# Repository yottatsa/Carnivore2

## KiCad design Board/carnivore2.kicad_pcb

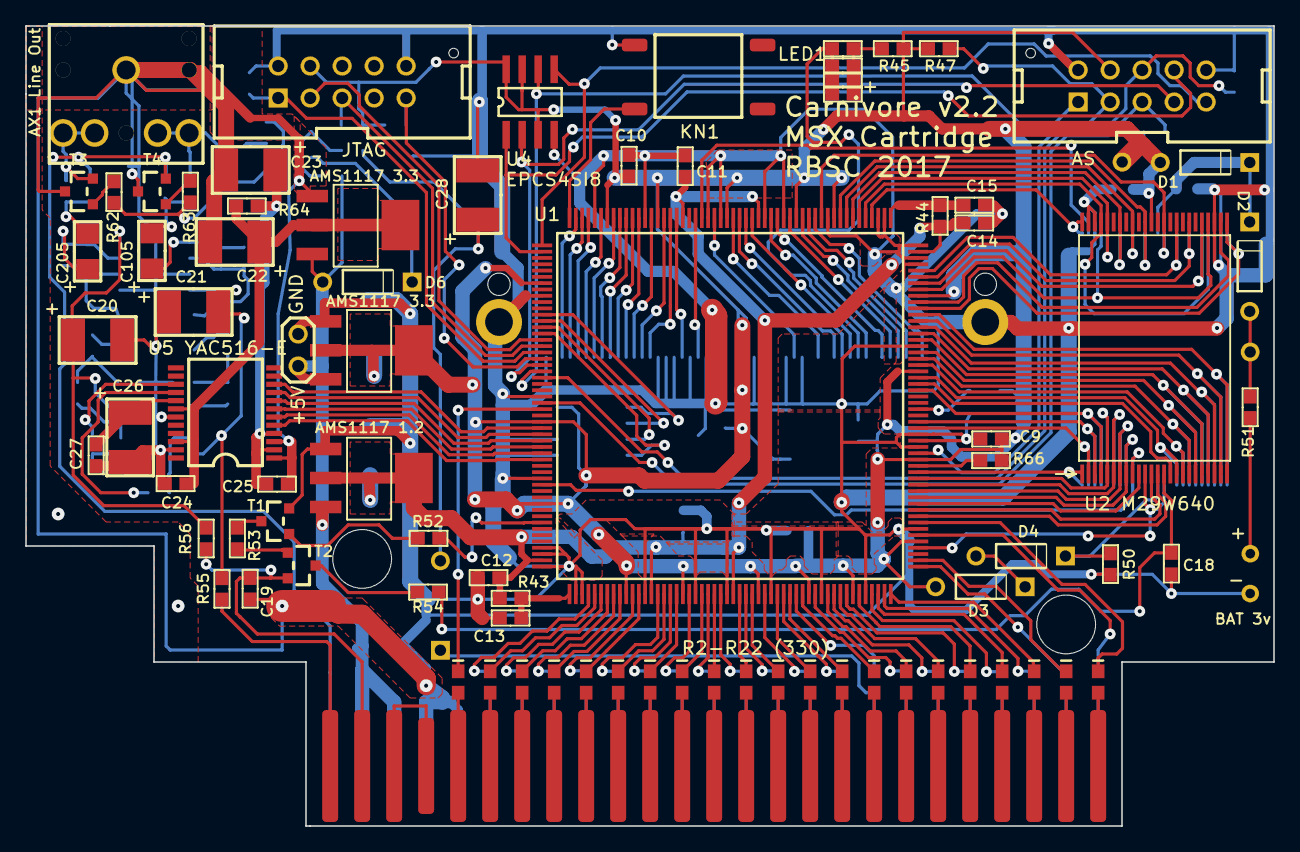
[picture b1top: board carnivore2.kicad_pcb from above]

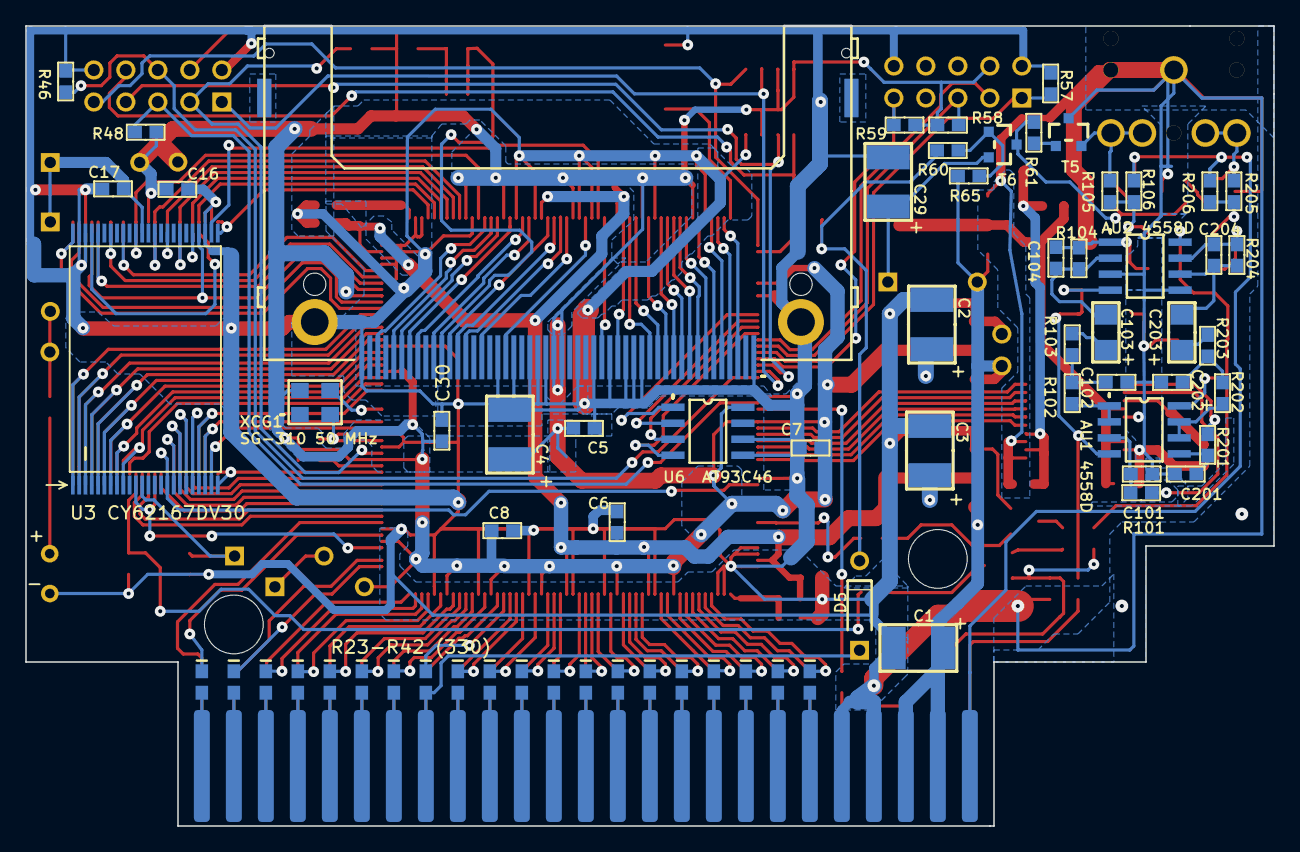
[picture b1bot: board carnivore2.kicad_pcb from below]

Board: 2 copper layers, 99.1 x 63.5 mm, 151 parts (69 on the bottom side), 220 nets.

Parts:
.1: KNS01_1
.2: EDGE50/MSX_1
.3: JUMPER_1
.6, .7: IDC10M_1
AU1, AU2: 4558D_1
AX1: {Value}; ST-222_1
C1, C2, C3, C4, C22, C23, C26, C28: 10mk; C_1812_1
C5, C6, C7, C8, C9, C10, C11, C12, C13, C14, C15, C16, C17, C18, C19, C24, C25, C27, C30: 0.1mk; C_0603_1
C20, C21: 100mk 16v; C_1812_1
C29: 22mk; C_1812_1
C101, C102, C201, C202: 1n; C_0603_1
C103, C105, C203, C205: 4.7mk 25v; C_1206_1
C104, C204: 390p; C_0603_1
D1, D2: D9; DIODE_1N4148_1
D3, D4, D5, D6: 1N4148; DIODE_1N4148_1
LED1, LED2, LED3, LED4: C_0603_1
R2, R3, R4, R5, R6, R7, R8, R9, R10, R11, R12, R13, R14, R15, R16, R17, R18, R19, R20, R21, R22, R23, R24, R25, R26, R27, R28, R29, R30, R31, R32, R33, R34, R35, R36, R37, R38, R39, R40, R41, R42: 331; C0603_1
R43, R44, R54, R64: 10; R_0603_1
R45, R55, R56: 220; R_0603_1
R46, R47, R48, R50, R52, R60, R65, R66, R101, R201: 10k; R_0603_1
R51, R58, R59, R106, R206: 1k; R_0603_1
R53, R61, R62, R63: 2.2k; R_0603_1
R57: 1K; R_0603_1
R102, R103, R202, R203: 4.7k; R_0603_1
R104, R204: 100k; R_0603_1
R105, R205: 1.8k; R_0603_1
T1, T3, T4, T5: 2SC945; SOT-23(A1A2K)_1
T2, T6: 2SA733; SOT-23(A1A2K)_1
U1: EP2C5Q208C8_1
U2: M29W320DXXXNXX_1
U3: CY62167DV30_1
U4: EPCS4SI8_1
U5: YAC516-E_1
U6: M93C46MN1_1
U7: 50 MHz; SG-310_1
UCT1: 1.2v; ADP3338_1
UCT2, UCT3: 3.3v; ADP3338_1
XC1: CF-50-001_1

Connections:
+AV12: AU1.8, AU2.8, C20.2, R56.1
-AV12: AU1.4, AU2.4, C21.1, R55.1
-V12: .2.50, R55.2
A0: .2.28, R9.2
A1: .2.27, R36.2
A2: .2.30, R8.2
A3: .2.29, R37.2
A4: .2.32, R7.2
A5: .2.31, R38.2
A6: .2.22, R12.2
A7: .2.21, R33.2
A8: .2.24, R11.2
A9: .2.17, R31.2
A10: .2.20, R13.2
A11: .2.19, R32.2
A12: .2.23, R34.2
A13: .2.26, R10.2
A14: .2.25, R35.2
A15: .2.18, R14.2
ADSO: .6.9, U1.1, U4.5
BICK: U1.32, U5.8
CE2: D4.2, R50.2, U3.12
CF_LED: LED1.1, LED2.1, LED3.1, LED4.1, XC1.45
CKS: U1.33, U5.7
CLC: .2.42, R2.2
CONF_DONE: .6.3, R47.2, U1.123
D0: .2.34, R6.2
D1: .2.33, R39.2
D2: .2.36, R5.2
D3: .2.35, R40.2
D4: .2.38, R4.2
D5: .2.37, R41.2
D6: .2.40, R3.2
D7: .2.39, R42.2
DATA0: .6.7, U1.20, U4.2
DCLK: .6.1, U1.21, U4.6
EECK: U1.13, U6.2
EECS: U1.12, U6.1
EEDI: U1.14, U6.3
EEDO: U1.15, U6.4
GND: .1.4, .2.41, .2.43, .3.C1, .6.2, .6.10, .7.2, .7.10, AU2.3, AU2.5, AX1.1, C1.1, C2.1, C3.1, C4.1, C5.1, C6.1, C7.1, C8.1, C9.1, C10.2, C11.2, C12.1, C13.1, C14.2, C15.2, C16.1, C17.2, C18.1, C19.2, C20.1, C21.2, C22.1, C23.1, C24.1, C25.1, C26.1, C27.1, C28.1, C29.1, C30.1, C101.1, C102.2, C201.1, C202.2, R46.1, R50.1, R57.1, T1.A2, T3.K, T4.K, T5.K, U1.9, U1.25, U1.38, U1.49, U1.50, U1.52, U1.54, U1.55, U1.65, U1.73, U1.78, U1.85, U1.93, U1.100, U1.111, U1.124, U1.125, U1.126, U1.140, U1.153, U1.154, U1.156, U1.158, U1.159, U1.167, U1.174, U1.177, U1.184, U1.186, U1.196, U1.204, U2.27, U2.46, U2.47, U3.27, U3.46, U3.47, U4.4, U5.1, U5.3, U5.19, U5.23, U6.5, U6.6, U7.2, UCT1.1, UCT2.1, UCT3.1, XC1.1, XC1.8, XC1.9, XC1.10, XC1.11, XC1.12, XC1.14, XC1.15, XC1.16, XC1.17, XC1.33, XC1.39, XC1.50, XC1.51, XC1.52
HA0: U1.179, XC1.20
HA1: U1.181, XC1.19
HA2: U1.182, XC1.18
HD0: U1.176, XC1.21
HD1: U1.175, XC1.22
HD2: U1.171, XC1.23
HD3: U1.207, XC1.2
HD4: U1.205, XC1.3
HD5: U1.201, XC1.4
HD6: U1.199, XC1.5
HD7: U1.197, XC1.6
HD8: U1.173, XC1.47
HD9: U1.170, XC1.48
HD10: U1.169, XC1.49
HD11: U1.206, XC1.27
HD12: U1.203, XC1.28
HD13: U1.200, XC1.29
HD14: U1.198, XC1.30
HD15: U1.195, XC1.31
KN0: .1.3, U1.208
LAUDIOR: AX1.2, AX1.3, R205.2, T5.A2
LAUDOL: AX1.4, AX1.5, R105.2, T3.A2
LRCK: U1.30, U5.10
MCLK: U1.34, U5.6
NCE: .6.6, R46.2, U1.22
NCONFIG: .6.5, R48.2, U1.26
NCS0: .6.8, U1.2, U4.1
NET00000: U1.130, U7.3
NET00004: R52.1, T1.A1
NET00005: R53.1, T1.K
NET00006: R53.2, T2.A1
NET00007: .2.44, .2.46
NET00008: R54.1, T2.K
NET00018: C13.2, R43.2, U1.53
NET00019: C15.1, R44.1, U1.157
NET00020: U1.180, XC1.44
NET00022: D2.1, R51.2
NET00024: D3.2, D4.1
NET00025: C23.2, C25.2, R64.2, U5.2, U5.4
NET00026: LED1.2, LED2.2, LED3.2, LED4.2, R45.1
NET00027: AU1.3, C101.2, R101.2
NET00028: AU1.1, AU1.2, R102.1
NET00029: C102.1, R102.2, R103.1
NET00031: C103.1, R103.2
NET00033: AU2.2, C103.2, C104.1, R104.1
NET00036: AU1.5, C201.2, R201.2
NET00037: AU1.6, AU1.7, R202.1
NET00038: C202.1, R202.2, R203.1
NET00040: C203.1, R203.2
NET00041: AU2.6, C203.2, C204.1, R204.1
NET00042: C205.2, R205.1, R206.1
NET00045: AU2.7, C204.2, C205.1, R204.2
NET00046: C105.2, R105.1, R106.1
NET00047: R62.2, T5.A1
NET00048: R63.2, T4.A1
NET00049: R61.2, T3.A1
NET00050: R61.1, R62.1, R63.1, T6.K
NET00051: C29.2, D6.2, T6.A2
NET00052: R60.1, R65.2, T6.A1
NET00053: C28.2, D5.1, R60.2
NET00054: R201.1, U5.15
NET00055: R101.1, U5.16
NET00057: C26.2, C27.2, U5.17
NET00058: AU2.1, C104.2, C105.1, R104.2
NSTATUS: R66.1, U1.121
RA0: U1.146, U2.25, U3.48
RA1: U1.145, U2.24, U3.1
RA2: U1.144, U2.23, U3.2
RA3: U1.143, U2.22, U3.3
RA4: U1.142, U2.21, U3.4
RA5: U1.141, U2.20, U3.5
RA6: U1.139, U2.19, U3.6
RA7: U1.138, U2.18, U3.7
RA8: U1.116, U2.8, U3.17
RA9: U1.117, U2.7, U3.18
RA10: U1.118, U2.6, U3.19
RA11: U1.119, U2.5, U3.20
RA12: U1.133, U2.4, U3.21
RA13: U1.128, U2.3, U3.22
RA14: U1.127, U2.2, U3.23
RA15: U1.120, U2.1, U3.24
RA16: U1.160, U2.48, U3.25
RA17: U1.137, U2.17, U3.8
RA18: U1.135, U2.16, U3.9
RA19: U1.39, U2.9, U3.16
RA20: U1.115, U2.10
RA21: U1.113, U2.13
RDQ0: U1.150, U2.29, U3.44
RDQ1: U1.151, U2.31, U3.42
RDQ2: U1.152, U2.33, U3.40
RDQ3: U1.168, U2.35, U3.38
RDQ4: U1.165, U2.38, U3.35
RDQ5: U1.164, U2.40, U3.33
RDQ6: U1.163, U2.42, U3.31
RDQ7: U1.162, U2.44, U3.29
RDQ15A-1: U1.161, U2.45, U3.45
RSW1: .2.16, R15.2
RSW2: .2.5, R25.2
RVPPE: R52.2, U1.45
R~E: U1.147, U2.26
R~G: U1.149, U2.28, U3.28
R~RB: U1.134, U2.15
R~RP: U1.114, U2.12
R~W: U1.108, U2.11, U3.11
SDATA: U1.31, U5.9
SLTA0: R9.1, U1.74
SLTA1: R36.1, U1.72
SLTA2: R8.1, U1.70
SLTA3: R37.1, U1.69
SLTA4: R7.1, U1.68
SLTA5: R38.1, U1.67
SLTA6: R12.1, U1.82
SLTA7: R33.1, U1.81
SLTA8: R11.1, U1.80
SLTA9: R31.1, U1.87
SLTA10: R13.1, U1.86
SLTA11: R32.1, U1.84
SLTA12: R34.1, U1.77
SLTA13: R10.1, U1.76
SLTA14: R35.1, U1.75
SLTA15: R14.1, U1.88
SLTCLC: R2.1, U1.27
SLTD0: R6.1, U1.64
SLTD1: R39.1, U1.63
SLTD2: R5.1, U1.61
SLTD3: R40.1, U1.60
SLTD4: R4.1, U1.59
SLTD5: R41.1, U1.58
SLTD6: R3.1, U1.57
SLTD7: R42.1, U1.56
SLTRSW2: R25.1, U1.103
SLTSOUND: .2.49, R106.2, R206.2, T4.A2
SLT_MREQ: R17.1, U1.96
SLT~BUSDIR: R18.1, U1.99
SLT~CS1: R23.1, U1.110
SLT~CS2: R22.1, U1.112
SLT~CS12: R24.1, U1.105
SLT~INT: R19.1, U1.102
SLT~IORQ: R28.1, U1.95
SLT~M1: R27.1, U1.97
SLT~RD: R16.1, U1.94
SLT~RESET: R30.1, U1.89
SLT~RFSH: R20.1, U1.104
SLT~SLTSL: R21.1, U1.106
SLT~WAIT: R26.1, U1.101
SLT~WR: R29.1, U1.92
STLRSW1: R15.1, U1.90
TCK: .7.1, R57.2, U1.18
TDI: .7.9, R59.2, U1.19
TDO: .7.3, U1.16
TMS: .7.5, R58.2, U1.17
V1.2: C3.2, C6.2, C11.1, C12.2, C14.1, R43.1, R44.2, U1.51, U1.66, U1.79, U1.155, U1.178, U1.190, UCT1.2, UCT1.4
V3.3: .6.4, .7.4, C2.2, C4.2, C5.2, C7.2, C8.2, C9.2, C10.1, C16.2, C30.2, D1.1, D3.1, R45.2, R47.1, R48.1, R58.1, R59.1, R66.2, U1.7, U1.29, U1.42, U1.62, U1.71, U1.83, U1.91, U1.98, U1.109, U1.122, U1.136, U1.148, U1.166, U1.172, U1.183, U1.194, U1.202, U2.37, U4.3, U4.7, U4.8, U6.8, U7.4, UCT2.2, UCT2.4, XC1.13, XC1.38
V12: .2.48, C19.1, R56.2, T2.A2
VCC5: .2.45, .2.47, .3.C2, C1.2, D6.1, R65.1, UCT1.3, UCT2.3, UCT3.3
VCCRAM: C17.1, D1.2, D2.2, U3.37
VDDDA: C22.2, C24.2, R64.1, U5.18, U5.22, UCT3.2, UCT3.4
VPP12: C18.2, R54.2, U2.14
~BUSDIR: .2.10, R18.2
~CS1: .2.1, R23.2
~CS2: .2.2, R22.2
~CS12: .2.3, R24.2
~CSRAM: U1.187, U3.26
~HCS1: U1.193, XC1.7
~HCS3: U1.192, XC1.32
~HRD: U1.191, XC1.34
~HRST: U1.185, XC1.41
~HWR: U1.188, XC1.35
~IC: U1.35, U5.5
~INT: .2.8, R19.2
~IORQ: .2.11, R28.2
~M1: .2.9, R27.2
~MREQ: .2.12, R17.2
~RD: .2.14, R16.2
~RESET: .2.15, D5.2, R30.2
~RFSH: .2.6, R20.2
~SLTSL: .2.4, R21.2
~WAIT: .2.7, R26.2
~WR: .2.13, R29.2

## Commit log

2024-02-07 set up gnu make to work with linux as80
2024-02-07 initial support for MX29LV640EB
2024-02-07 macdev, debug output
2024-02-07 quick and dirty `Double Byte Program` revert
2024-02-12 re-creation of PCB in KiCAD for 3D modelling purpose
